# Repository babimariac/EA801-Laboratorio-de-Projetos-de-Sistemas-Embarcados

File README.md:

# EA801

Este repositório apresenta os projetos desenvolvidos na disciplina de graduação denominada Laboratório de Sistemas Embarcados da FEEC-UNICAMP.

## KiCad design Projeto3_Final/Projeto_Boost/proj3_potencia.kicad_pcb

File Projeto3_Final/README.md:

# Conversor Boost Utilizando Raspberry Pi Pico W: Uma Solução de Potência Versátil para Sistemas Embarcados

## Visão Geral do Projeto

Este projeto, desenvolvido com a placa BitDogLab e o microcontrolador Raspberry Pi Pico W, tem como objetivo principal a concepção e integração de um robusto circuito de potência baseado em um conversor DC-DC step-up, conhecido como conversor **boost**. A motivação para tal reside na crescente demanda por flexibilidade na alimentação de componentes em sistemas embarcados modernos. Para uma análise detalhada, o documento completo está [disponível aqui](https://docs.google.com/document/d/1OuxyFDfI4rMv4tx7KyJrpwKmmSDGhWM3hd5obKrCM_8/edit?tab=t.0), onde se explora como microcontroladores operam tipicamente com baixas tensões (como os 3.3V do Raspberry Pi Pico W), enquanto muitos atuadores essenciais – como motores, LEDs de alta potência e outros dispositivos – requerem tensões significativamente maiores para operar de forma eficiente.

Este projeto tem como objetivo desenvolver e integrar um circuito de potência baseado em um conversor DC-DC step-up (boost) com a placa BitDogLab, utilizando o microcontrolador Raspberry Pi Pico W. Enquanto microcontroladores operam tipicamente com baixas tensões (como 3.3V do microcontrolador em uso), muitos atuadores, como motores e LEDs de alta potência, exigem tensões significativamente maiores.

Neste cenário, o conversor boost surge como uma solução indispensável, permitindo otimizar o uso da energia disponível e expandir as capacidades intrínsecas do sistema. O controle preciso do conversor é realizado diretamente pelo Raspberry Pi Pico W, aproveitando sua capacidade de geração de sinais PWM (Pulse Width Modulation). Para garantir a segurança e a integridade do microcontrolador, esse sinal PWM é isolado galvanicamente através de um optoacoplador (o modelo U3 - 4N25 é utilizado), e subsequentemente amplificado por um gate driver discreto (composto pelos transistores Q2, Q3, Q4 e componentes associados) antes de acionar um MOSFET de potência (D3 - IRF540N), que é o componente chave para a conversão.

## A Crucial Importância do Circuito de Potência (Conversor Boost)

O circuito de potência, com o conversor boost em seu cerne, representa a fundação e a capacidade de "musculatura" deste projeto. Sua importância é inquestionável em qualquer sistema embarcado que exija acionamento de dispositivos com requisitos de tensão mais elevados do que o microcontrolador pode fornecer diretamente. A flexibilidade que o boost converter oferece é uma virada de jogo, permitindo que dispositivos de baixa potência, como o Pico W, controlem cargas de média a alta potência. Mais detalhes sobre essa funcionalidade podem ser encontrados no [documento completo do projeto](https://docs.google.com/document/d/1OuxyFDfI4rMv4tx7KyJrpwKmmSDGhWM3hd5obKrCM_8/edit?tab=t.0).

A relevância do conversor é destacada no texto principal:
> "Neste contexto, conversores DC-DC step-up, ou 'boost', tornam-se indispensáveis para otimizar o uso da energia disponível e expandir as capacidades do sistema."

Além de elevar a tensão, a arquitetura do circuito de potência implementada neste projeto foi cuidadosamente projetada para garantir robustez e segurança. A utilização de **planos de terra separados** (GND1 para a parte de controle da BitDogLab e GND2 para a parte de potência do circuito boost) é uma estratégia fundamental para mitigar a propagação de ruídos elétricos, gerados pelas rápidas comutações do MOSFET, para a sensível lógica digital do microcontrolador. Essa medida previne interferências e assegura a estabilidade do sistema.

O robusto gate driver discreto (com transistores como BC337, BD140, BD139) é vital para o acionamento eficiente do MOSFET. Ele é capaz de fornecer a corrente necessária para carregar e descarregar rapidamente a capacitância de porta do MOSFET, garantindo uma comutação ágil e minimizando perdas. O dimensionamento deste conversor em particular foi otimizado para uma tensão de entrada de 5V e uma saída regulada de 12V, com capacidade para fornecer até 1A de corrente à carga, resultando em uma potência de saída de 12W. Essa capacidade de amplificação de tensão, combinada com o isolamento e a proteção, torna o circuito de potência um pilar para diversas aplicações. Para informações adicionais sobre o dimensionamento, consulte o [documento do projeto](https://docs.google.com/document/d/1OuxyFDfI4rMv4tx7KyJrpwKmmSDGhWM3hd5obKrCM_8/edit?tab=t.0).

## Funcionalidades e Componentes Chave

O desenvolvimento do projeto seguiu uma abordagem dividida em etapas bem definidas para garantir a sua funcionalidade e robustez, conforme descrito em detalhes no [documento completo](https://docs.google.com/document/d/1OuxyFDfI4rMv4tx7KyJrpwKmmSDGhWM3hd5obKrCM_8/edit?tab=t.0):

1.  **Design e Dimensionamento do Circuito Conversor Boost:** Esta fase envolveu a definição precisa dos requisitos de entrada e saída (tensão, corrente, potência), a seleção criteriosa e o dimensionamento de todos os componentes críticos. Isso inclui os componentes do gate driver discreto (transistores, resistores, diodo de proteção), o MOSFET de potência (série IRF), o indutor de potência (com núcleo de ferrite) e os capacitores de entrada/saída, além do diodo do conversor Boost. O esquemático detalhado foi elaborado no KiCad, uma ferramenta essencial para a validação das conexões e valores dos componentes.

2.  **Implementação do Firmware e Controle do Pico W:** Esta etapa focou na configuração e programação do módulo PWM do microcontrolador RP2040. O objetivo foi gerar pulsos de controle com a frequência e duty cycle exatos necessários para o funcionamento otimizado do conversor boost, utilizando a GPIO 20 do Raspberry Pi Pico W. Foi fundamental estabelecer uma interface robusta entre o Pico W e o circuito de potência, assegurando a correta utilização dos GPIOs configurados para PWM, a compatibilidade dos níveis lógicos e a operação segura do optoacoplador e do gate driver.

**Componentes de Hardware Utilizados:**

Uma lista completa e detalhada dos componentes de hardware, juntamente com suas funções específicas e diagramas, pode ser consultada no [documento do projeto](https://docs.google.com/document/d/1OuxyFDfI4rMv4tx7KyJrpwKmmSDGhWM3hd5obKrCM_8/edit?tab=t.0). Alguns dos principais incluem:

*   **Placa BitDogLab:** Atua como a base de desenvolvimento principal para o microcontrolador.
*   **Raspberry Pi Pico W (RP2040):** O coração do controle, um microcontrolador dual-core com módulos PWM de alta resolução.
*   **Optoacoplador 4N25 (U3):** Garante o isolamento galvânico crítico do sinal PWM de controle, protegendo o microcontrolador.
*   **Transistores de Sinal e Potência (Q2 - BC337, Q3 - BD140, Q4 - BD139):** Compõem o gate driver discreto, responsáveis pela amplificação e acionamento eficiente do MOSFET.
*   **MOSFET de Potência (D3 - IRF540N):** O dispositivo chave de comutação do conversor boost, adequado para as tensões e correntes envolvidas.
*   **Indutor de Potência (L2):** Um elemento fundamental para o armazenamento e transferência de energia no conversor.
*   **Diodo de Recuperação Rápida ou Schottky (incorporado no D3 e D1 no driver):** Essencial para a retificação da saída do boost.
*   **Resistores diversos (R2, R3, R4, R5, R6, R7, R8, R10):** Utilizados para polarização, limitação de corrente e funções de pull-up/down.
*   **Capacitores Eletrolíticos (C1 - 10μF, C2 - 10μF):** Capacitores de baixa ESR (Equivalent Series Resistance) para filtragem de entrada e saída, e possível C3 para desacoplamento.
*   **Diodos de Proteção (D1, D3 - corpo diode):** Oferecem proteção contra transientes de tensão e durante o chaveamento.
*   **Terminais e Conectores (J1, J2, J3, J4, J5):** Para as conexões de potência, carga, PWM e outras necessidades.
*   **LED Indicador (D2) com Resistor Limitador (R7):** Fornece feedback visual do status, indicando que há tensão na entrada.

**Software e Linguagens Utilizadas:**

A implementação do software foi crucial para o controle do sistema, e os detalhes técnicos podem ser explorados no [material de apoio](https://docs.google.com/document/d/1OuxyFDfI4rMv4tx7KyJrpwKmmSDGhWM3hd5obKrCM_8/edit?tab=t.0). As principais ferramentas e linguagens incluem:

*   **Linguagem C:** A linguagem de programação utilizada para o firmware, aproveitando o SDK oficial da Raspberry Pi.
*   **Raspberry Pi Pico C/C++ SDK:** O SDK oficial que oferece suporte aos módulos GPIO, ADC, PWM e outros recursos necessários para o controle.
*   **CMake:** O sistema de build empregado para compilar e organizar o projeto C/C++.
*   **KiCad:** Software fundamental para a elaboração e validação do esquemático e do layout da placa de circuito impresso (PCB).

## Implementação de Firmware

A capacidade de controle do Raspberry Pi Pico W é demonstrada na implementação do firmware, que gerencia o sinal PWM para o conversor boost. O código foi configurado para uma operação precisa, e o trecho fundamental para a configuração do PWM é apresentado no [documento do projeto](https://docs.google.com/document/d/1OuxyFDfI4rMv4tx7KyJrpwKmmSDGhWM3hd5obKrCM_8/edit?tab=t.0):

*   **Pino de Saída do PWM:** Definido como `GPIO 20`.
*   **Frequência do PWM:** Estabelecida em `100 kHz`.
*   **Duty Cycle do PWM:** Configurado em `55%`.

Essa configuração é essencial para o chaveamento adequado do MOSFET e, consequentemente, para a elevação da tensão na saída do conversor.

```c
#define PWM_OUTPUT_PIN 20 // Define o pino do PWM

// Configuração do PWM:
gpio_set_function(PWM_OUTPUT_PIN, GPIO_FUNC_PWM);
uint pwm_slice = pwm_gpio_to_slice_num(PWM_OUTPUT_PIN);
pwm_set_wrap(pwm_slice, 1249); // Frequência = 100kHz
pwm_set_chan_level(pwm_slice, pwm_gpio_to_channel(PWM_OUTPUT_PIN), 688); // Duty cycle = 55%
pwm_set_enabled(pwm_slice, true);

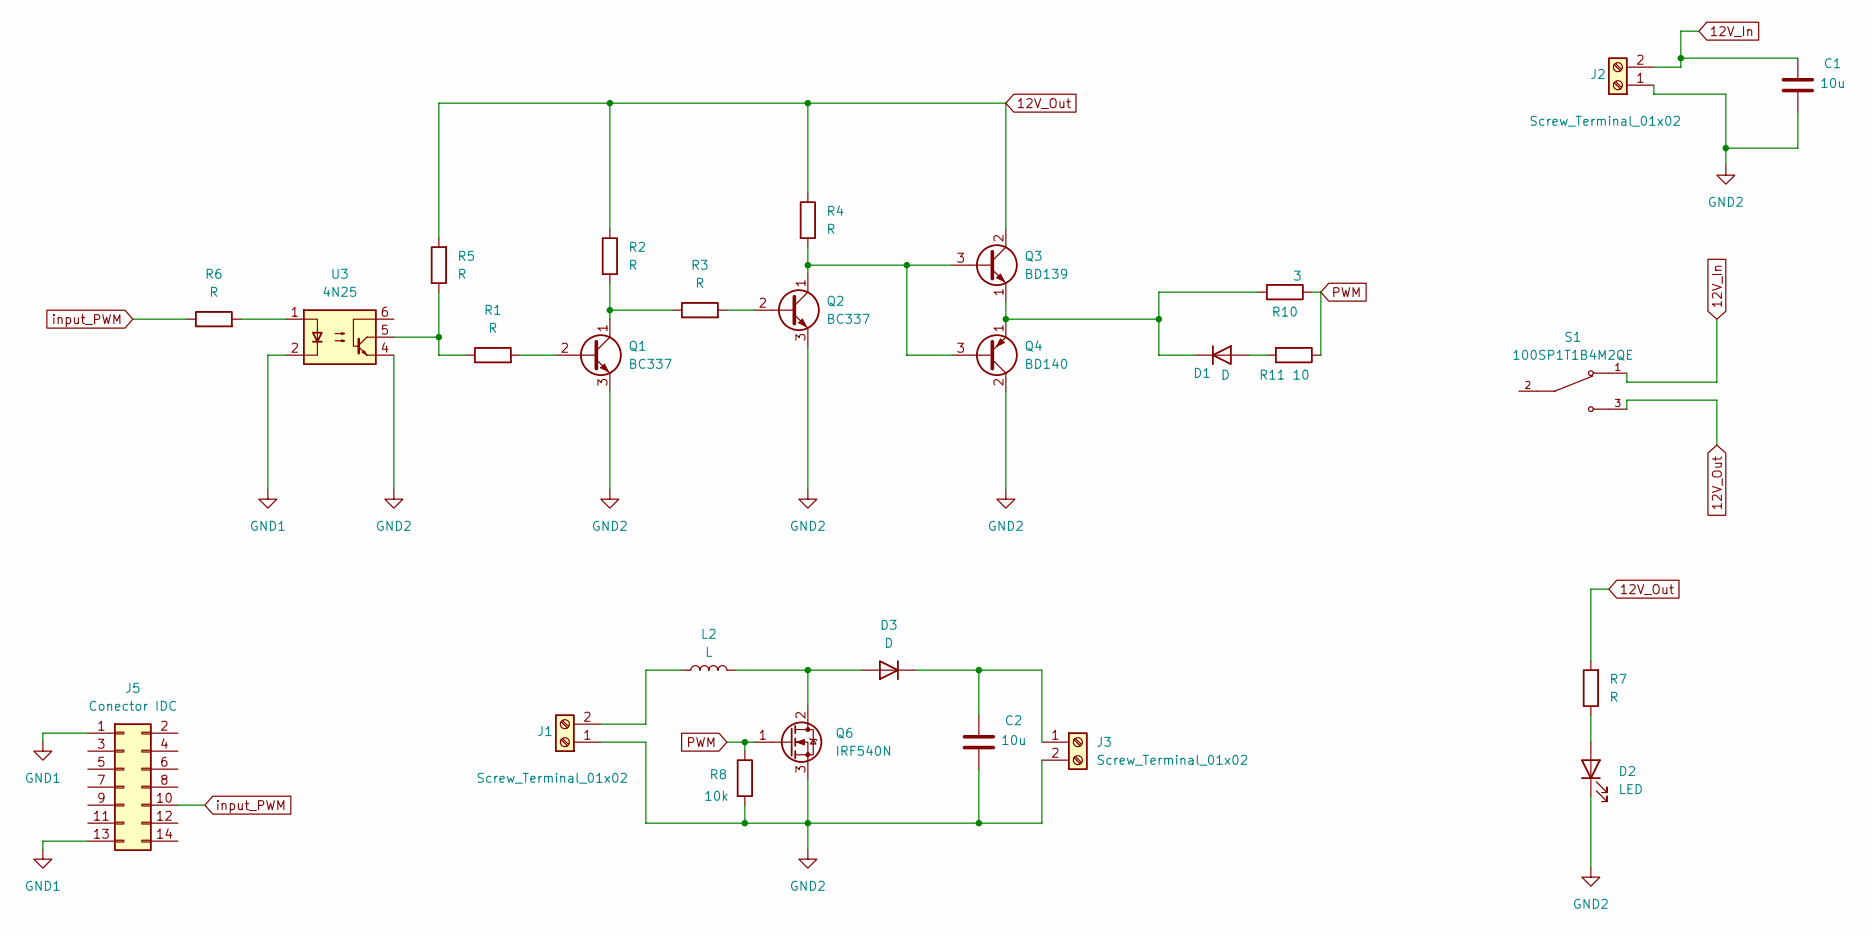
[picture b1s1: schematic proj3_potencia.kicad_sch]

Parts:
C1, C2: 10u; CP_Radial_D8.0mm_P5.00mm
D1, D3: D; D_5W_P10.16mm_Horizontal
D2: LED; LED_D3.0mm
J1, J2, J3: Screw_Terminal_01x02; TerminalBlock_Phoenix_MKDS-1,5-2-5.08_1x02_P5.08mm_Horizont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
J5: Conector IDC; PinHeader_2x07_P2.54mm_Vertical
L2: L; L_Toroid_Vertical_L26.7mm_W14.0mm_P10.16mm_Pulse_D
Q1, Q2: BC337; TO-92_Inline
Q3: BD139; TO-126-3_Vertical
Q4: BD140; TO-126-3_Vertical
Q6: IRF540N; TO-220-3_Vertical
R1, R2, R3, R4, R5, R6, R7: R; R_Axial_DIN0309_L9.0mm_D3.2mm_P12.70mm_Horizontal
R8: 10k; R_Axial_DIN0309_L9.0mm_D3.2mm_P12.70mm_Horizontal
R10: 3; R_Axial_DIN0309_L9.0mm_D3.2mm_P12.70mm_Horizontal
R11: 10; R_Axial_DIN0309_L9.0mm_D3.2mm_P12.70mm_Horizontal
S1: 100SP1T1B4M2QE; SW_100SP1T1B4M2QE; PARTREV E
U3: 4N25; DIP-6_W7.62mm

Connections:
12V_In: C1.1, J2.2, S1.1
12V_Out: Q3.2 (C), R2.1, R4.1, R5.2, R7.2, S1.3
GND1: J5.1, J5.13, U3.2
GND2: C1.2, C2.2, D2.1 (K), J1.1, J2.1, J3.2, Q1.3 (E), Q2.3 (E), Q4.2 (C), Q6.3 (S), R8.2, U3.4
unnamed: D1.2 (A), R11.2
unnamed: D1.1 (K), Q3.1 (E), Q4.1 (E), R10.2
unnamed: D2.2 (A), R7.1
unnamed: D3.2 (A), L2.2, Q6.2 (D)
unnamed: C2.1, D3.1 (K), J3.1
unnamed: J1.2, L2.1
unnamed: Q1.2 (B), R1.2
unnamed: Q1.1 (C), R2.2, R3.1
unnamed: Q2.2 (B), R3.2
unnamed: Q2.1 (C), Q3.3 (B), Q4.3 (B), R4.2
unnamed: R1.1, R5.1, U3.5
unnamed: R6.2, U3.1
PWM: Q6.1 (G), R8.1, R10.1, R11.1
input_PWM: J5.10, R6.1

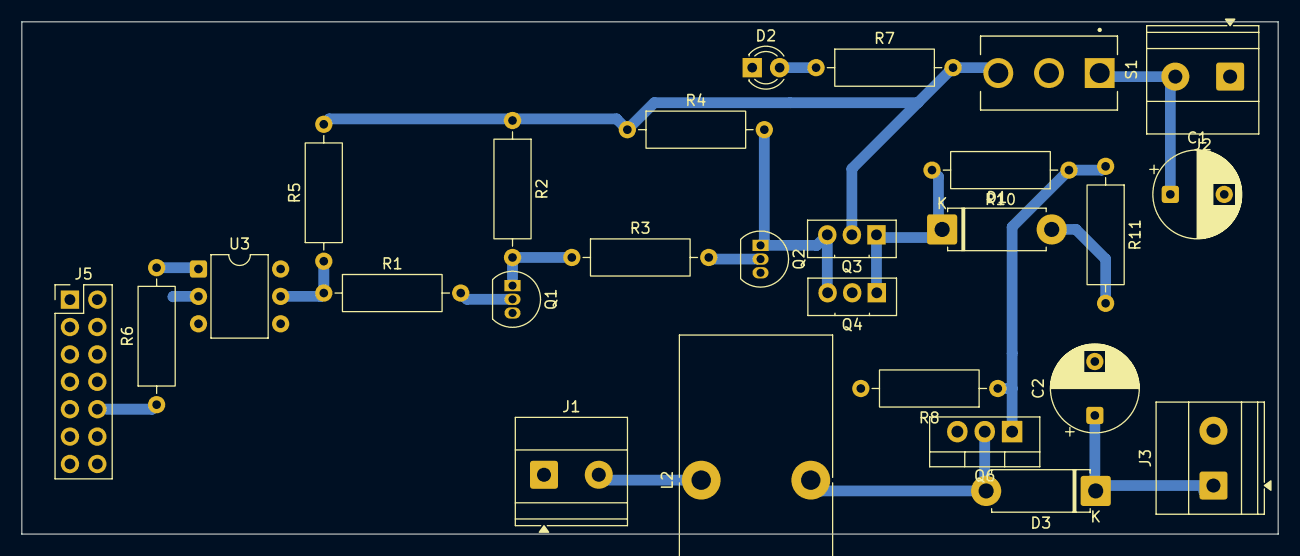
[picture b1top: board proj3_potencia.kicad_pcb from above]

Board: 2 copper layers, 116.5 x 47.5 mm, 27 parts (0 on the bottom side), 18 nets.
